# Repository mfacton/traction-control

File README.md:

# traction-control
Traction Control

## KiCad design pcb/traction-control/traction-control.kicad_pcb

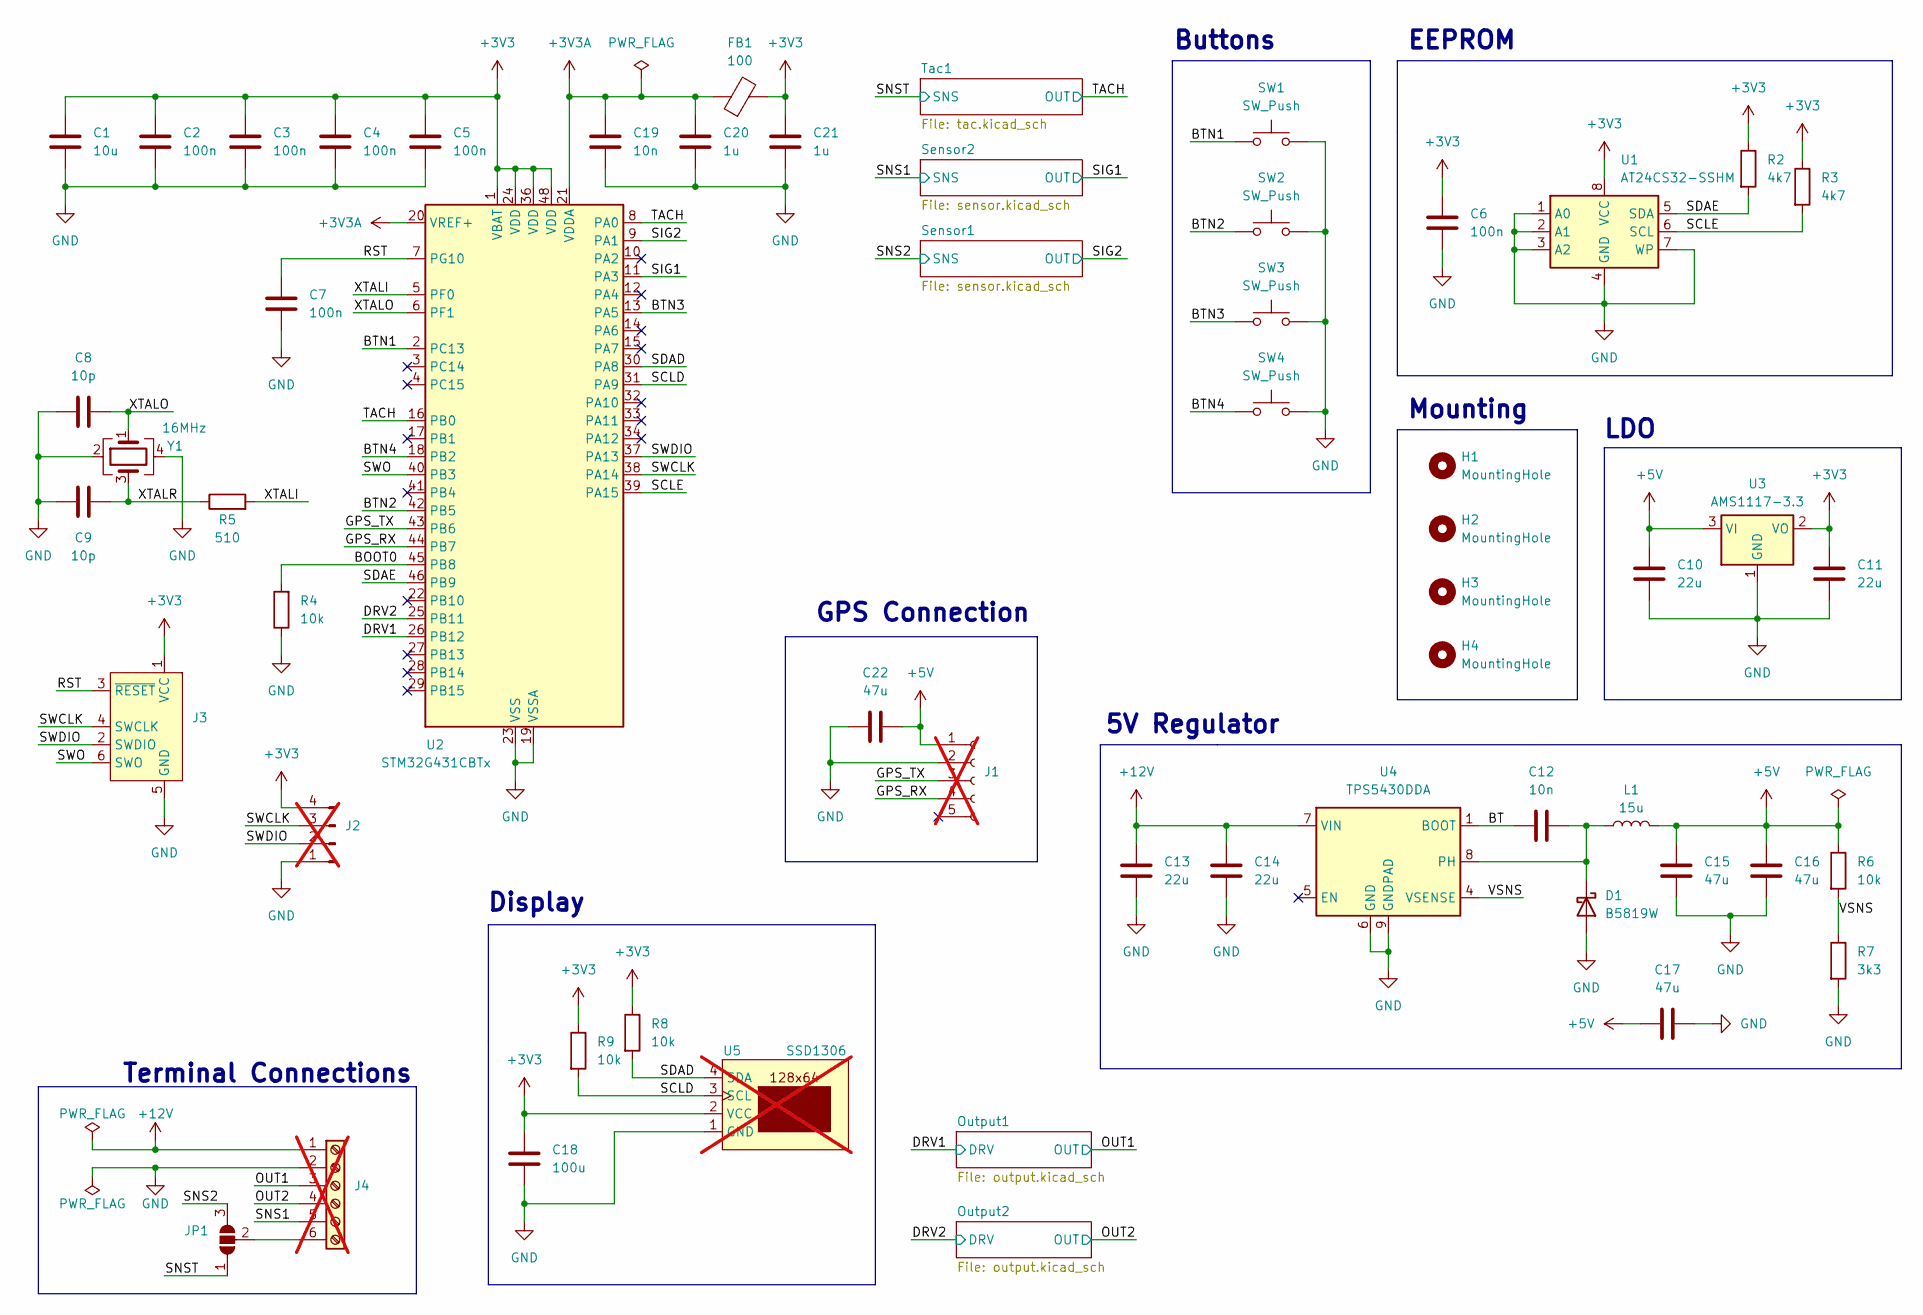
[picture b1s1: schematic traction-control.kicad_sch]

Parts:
C1: 10u; C_0402_1005Metric; LCSC C15525
C2, C3, C4, C5, C6, C7: 100n; C_0402_1005Metric; LCSC C1525
C8, C9: 10p; C_0402_1005Metric; LCSC C32949
C10: 22u; C_0805_2012Metric; LCSC C45783
C11: 22u; C_0603_1608Metric; LCSC C59461
C12, C19: 10n; C_0402_1005Metric; LCSC C15195
C13, C14: 22u; C_1206_3216Metric; LCSC C12891
C15, C16, C17, C22: 47u; C_1206_3216Metric; LCSC C96123
C18: 100u; C_1206_3216Metric; LCSC C15008
C20, C21: 1u; C_0402_1005Metric; LCSC C52923
D1: B5819W; D_SOD-123; LCSC C8598
FB1: 100; L_0805_2012Metric; LCSC C1015
H1, H2, H3, H4: MountingHole; MountingHole_3.2mm_M3
J1: Conn_01x05_Socket; PinHeader_1x05_P2.54mm_Vertical; not fitted
J2: Conn_01x04_Pin; PinHeader_1x04_P2.54mm_Vertical; not fitted
J3: Conn_ARM_SWD_TagConnect_TC2030-NL; Tag-Connect_TC2030-IDC-NL_2x03_P1.27mm_Vertical
J4: Screw_Terminal_01x06; ScrewTerminalPlug_6P_P5.08; not fitted
JP1: SolderJumper_3_Open; SolderJumper-3_P1.3mm_Open_RoundedPad1.0x1.5mm
L1: 15u; L_Changjiang_FNR6020S; LCSC C168015
R2, R3: 4k7; R_0402_1005Metric; LCSC C25900
R4, R6, R8, R9: 10k; R_0402_1005Metric; LCSC C25744
R5: 510; R_0402_1005Metric; LCSC C25123
R7: 3k3; R_0402_1005Metric; LCSC C25890
SW1, SW2, SW3, SW4: SW_Push; SW_Push_1P1T_NO_6x6mm_H9.5mm; LCSC C455119
U1: AT24CS32-SSHM; SOIC-8_3.9x4.9mm_P1.27mm; LCSC C6482
U2: STM32G431CBTx; LQFP-48_7x7mm_P0.5mm; LCSC C529355
U3: AMS1117-3.3; SOT-223-3_TabPin2; LCSC C6186
U4: TPS5430DDA; TI_SO-PowerPAD-8_ThermalVias; LCSC C9864
U5: SSD1306; SSD1309_1.3; not fitted
Y1: 16MHz; Crystal_SMD_3225-4Pin_3.2x2.5mm; LCSC C13738

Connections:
+3V3: C1.1, C2.1, C3.1, C4.1, C5.1, C6.1, C11.1, C18.1, C21.1, FB1.2, J2.4, J3.1 (VCC), R2.1, R3.1, R8.1, R9.1, U1.8 (VCC), U2.1 (VBAT), U2.24 (VDD), U2.36 (VDD), U2.48 (VDD), U3.2 (VO), U5.2 (VCC)
+3V3A: C19.1, C20.1, FB1.1, U2.20 (VREF+), U2.21 (VDDA)
+5V: C10.1, C15.1, C16.1, C17.1, C22.1, J1.1, L1.2, R6.1, U3.3 (VI)
+12V: C13.1, C14.1, J4.1, U4.7 (VIN); also elsewhere on the board
/BOOT0: R4.2, U2.45 (PB8)
/BT: C12.1, U4.1 (BOOT)
/BTN1: SW1.1, U2.2 (PC13)
/BTN2: SW2.1, U2.42 (PB5)
/BTN3: SW3.1, U2.13 (PA5)
/BTN4: SW4.1, U2.18 (PB2)
/DRV1: U2.26 (PB12); also elsewhere on the board
/DRV2: U2.25 (PB11); also elsewhere on the board
/GPS_RX: J1.4, U2.44 (PB7)
/GPS_TX: J1.3, U2.43 (PB6)
/OUT1: J4.3; also elsewhere on the board
/OUT2: J4.4; also elsewhere on the board
/RST: C7.1, J3.3 (~RESET), U2.7 (PG10)
/SCLD: R9.2, U2.31 (PA9), U5.3 (SCL)
/SCLE: R3.2, U1.6 (SCL), U2.39 (PA15)
/SDAD: R8.2, U2.30 (PA8), U5.4 (SDA)
/SDAE: R2.2, U1.5 (SDA), U2.46 (PB9)
/SIG1: U2.11 (PA3); also elsewhere on the board
/SIG2: U2.9 (PA1); also elsewhere on the board
/SNS1: J4.5; also elsewhere on the board
/SNS2: JP1.3 (B); also elsewhere on the board
/SNST: JP1.1 (A); also elsewhere on the board
/SWCLK: J2.3, J3.4 (SWCLK), U2.38 (PA14)
/SWDIO: J2.2, J3.2 (SWDIO), U2.37 (PA13)
/SWO: J3.6 (SWO), U2.40 (PB3)
/TACH: U2.8 (PA0), U2.16 (PB0); also elsewhere on the board
/VSNS: R6.2, R7.1, U4.4 (VSENSE)
/XTALI: R5.2, U2.5 (PF0)
/XTALO: C8.2, U2.6 (PF1), Y1.1
/XTALR: C9.2, R5.1, Y1.3
GND: C1.2, C2.2, C3.2, C4.2, C5.2, C6.2, C7.2, C8.1, C9.1, C10.2, C11.2, C13.2, C14.2, C15.2, C16.2, C17.2, C18.2, C19.2, C20.2, C21.2, C22.2, D1.2 (A), J1.2, J2.1, J3.5 (GND), J4.2, R4.1, R7.2, SW1.2, SW2.2, SW3.2, SW4.2, U1.1 (A0), U1.2 (A1), U1.3 (A2), U1.4 (GND), U1.7 (WP), U2.19 (VSSA), U2.23 (VSS), U2.35 (VSS), U2.47 (VSS), U3.1 (GND), U4.6 (GND), U4.9 (GNDPAD), U5.1 (GND), Y1.2, Y1.4; also elsewhere on the board
unnamed: C12.2, D1.1 (K), L1.1, U4.8 (PH)
unnamed: J4.6, JP1.2 (C)

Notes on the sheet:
GPS Connection
Mounting
EEPROM
LDO
Terminal Connections
5V Regulator
Display
Buttons

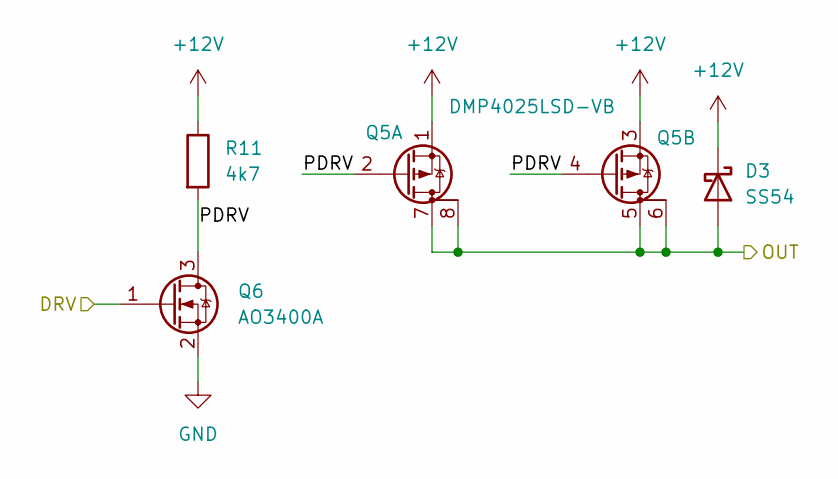
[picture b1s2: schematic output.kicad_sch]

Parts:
D3: SS54; D_SMA; LCSC C22452
Q5: DMP4025LSD-VB; SOP-8_3.9x4.9mm_P1.27mm; LCSC C725015
Q6: AO3400A; SOT-23; LCSC C20917
R11: 4k7; R_0402_1005Metric; LCSC C25900

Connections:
+12V: D3.1 (K), Q5.1 (S), Q5.3 (S), R11.1; also elsewhere on the board
/DRV2: Q6.1 (G); also elsewhere on the board
/OUT2: D3.2 (A), Q5.5 (D), Q5.6 (D), Q5.7 (D), Q5.8 (D); also elsewhere on the board
/Output2/PDRV: Q5.2 (G), Q5.4 (G), Q6.3 (D), R11.2
GND: Q6.2 (S); also elsewhere on the board

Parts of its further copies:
D2: SS54; D_SMA; LCSC C22452
Q3: DMP4025LSD-VB; SOP-8_3.9x4.9mm_P1.27mm; LCSC C725015
Q4: AO3400A; SOT-23; LCSC C20917
R10: 4k7; R_0402_1005Metric; LCSC C25900

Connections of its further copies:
+12V: D2.1 (K), Q3.1 (S), Q3.3 (S), R10.1; also elsewhere on the board
/DRV1: Q4.1 (G); also elsewhere on the board
/OUT1: D2.2 (A), Q3.5 (D), Q3.6 (D), Q3.7 (D), Q3.8 (D); also elsewhere on the board
/Output1/PDRV: Q3.2 (G), Q3.4 (G), Q4.3 (D), R10.2
GND: Q4.2 (S); also elsewhere on the board

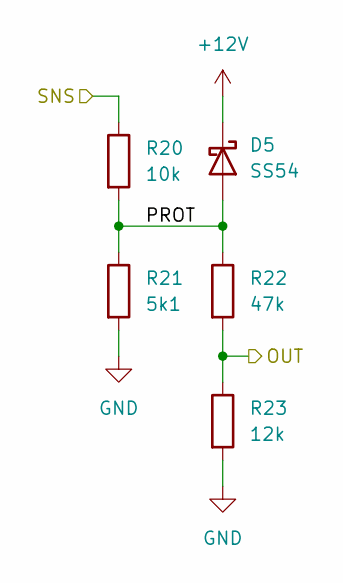
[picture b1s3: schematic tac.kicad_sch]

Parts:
D5: SS54; D_SMA; LCSC C22452
R20: 10k; R_0402_1005Metric; LCSC C25744
R21: 5k1; R_0402_1005Metric; LCSC C25905
R22: 47k; R_0402_1005Metric; LCSC C25792
R23: 12k; R_0402_1005Metric; LCSC C25752

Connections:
+12V: D5.1 (K); also elsewhere on the board
/SNST: R20.1; also elsewhere on the board
/TACH: R22.2, R23.1; also elsewhere on the board
/Tac1/PROT: D5.2 (A), R20.2, R21.1, R22.1
GND: R21.2, R23.2; also elsewhere on the board

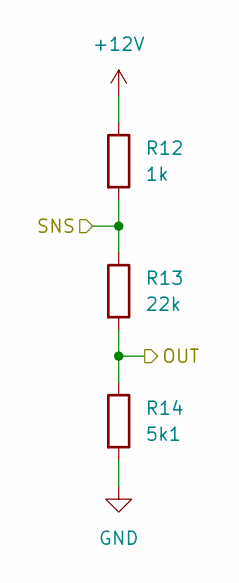
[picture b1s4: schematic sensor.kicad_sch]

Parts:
R12: 1k; R_1206_3216Metric; LCSC C4410
R13: 22k; R_0402_1005Metric; LCSC C25768
R14: 5k1; R_0402_1005Metric; LCSC C25905

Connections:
+12V: R12.1; also elsewhere on the board
/SIG1: R13.2, R14.1; also elsewhere on the board
/SNS1: R12.2, R13.1; also elsewhere on the board
GND: R14.2; also elsewhere on the board

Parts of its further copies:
R17: 1k; R_1206_3216Metric; LCSC C4410
R18: 22k; R_0402_1005Metric; LCSC C25768
R19: 5k1; R_0402_1005Metric; LCSC C25905

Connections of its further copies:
+12V: R17.1; also elsewhere on the board
/SIG2: R18.2, R19.1; also elsewhere on the board
/SNS2: R17.2, R18.1; also elsewhere on the board
GND: R19.2; also elsewhere on the board

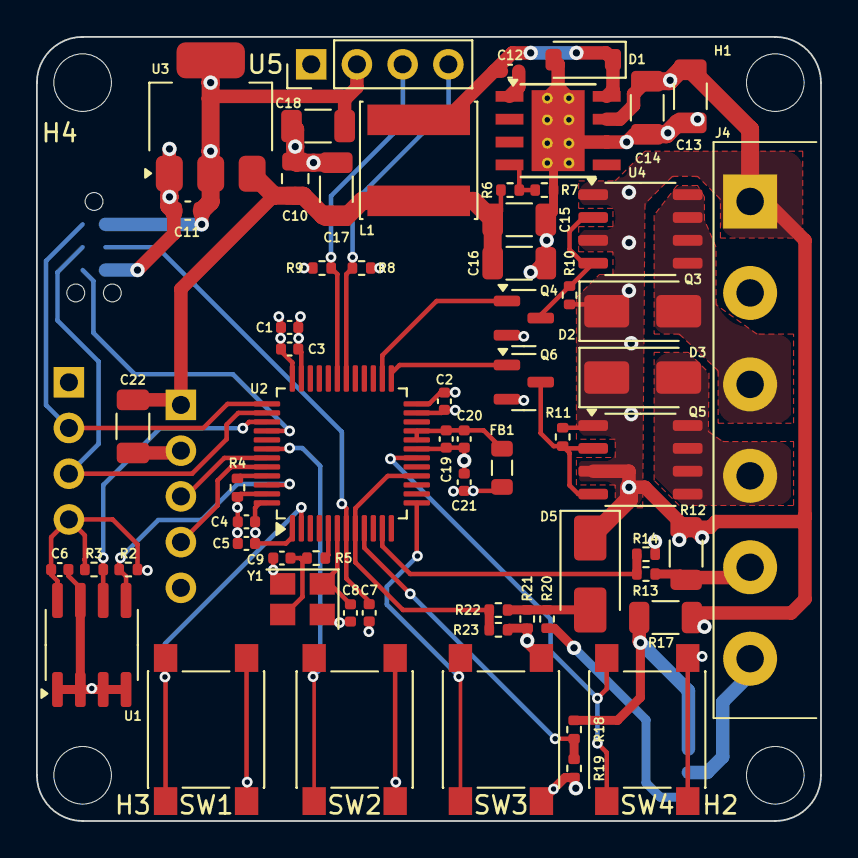
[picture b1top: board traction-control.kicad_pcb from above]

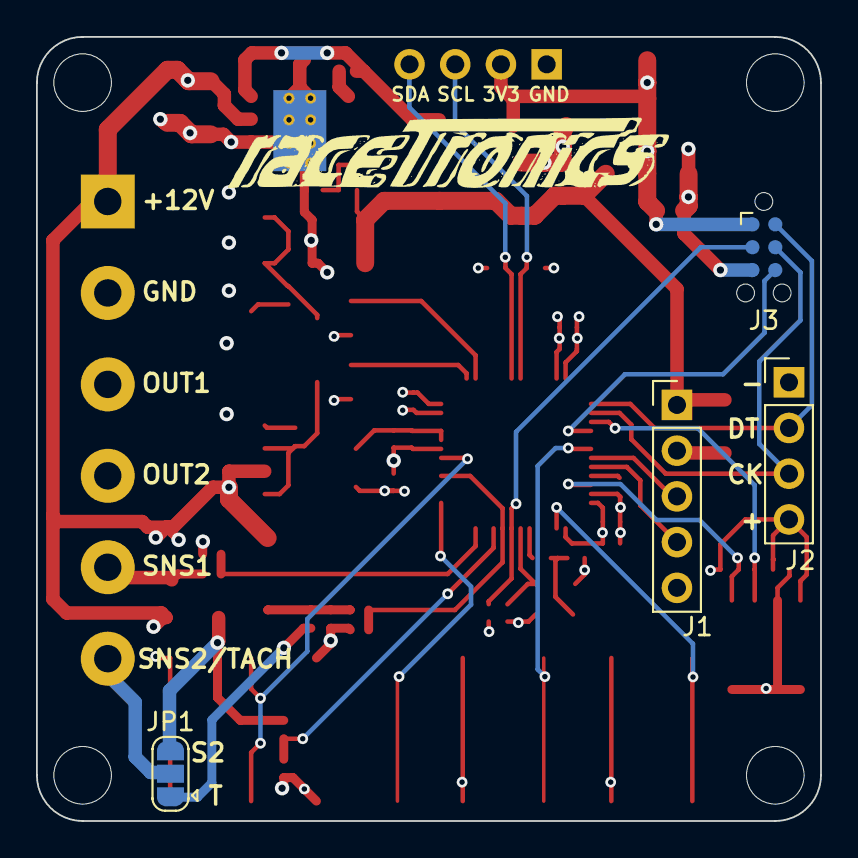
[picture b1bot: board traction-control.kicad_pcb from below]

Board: 4 copper layers, 43.6 x 43.6 mm, 72 parts (5 on the bottom side), 40 nets.

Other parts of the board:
G1: LOGO

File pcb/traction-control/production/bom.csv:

Designator,Footprint,Quantity,Value,LCSC Part #
C1,0402,1,10u,C15525
C10,0805,1,22u,C45783
C11,0603,1,22u,C59461
"C12, C19",0402,2,10n,C15195
"C13, C14",1206,2,22u,C12891
"C15, C16, C17, C22",1206,4,47u,C96123
C18,1206,1,100u,C15008
"C2, C3, C4, C5, C6, C7",0402,6,100n,C1525
"C20, C21",0402,2,1u,C52923
"C8, C9",0402,2,10p,C32949
D1,D_SOD-123,1,B5819W,C8598
"D2, D3, D5",D_SMA,3,SS54,C22452
FB1,0805,1,100,C1015
L1,L_Changjiang_FNR6020S,1,15u,C168015
"Q3, Q5",SOP-8_3.9x4.9mm_P1.27mm,2,DMP4025LSD-VB,C725015
"Q4, Q6",SOT-23,2,AO3400A,C20917
"R10, R11, R2, R3",0402,4,4k7,C25900
"R12, R17",1206,2,1k,C4410
"R13, R18",0402,2,22k,C25768
"R14, R19, R21",0402,3,5k1,C25905
"R20, R6, R8, R9",0402,4,10k,C25744
R22,0402,1,47k,C25792
R23,0402,1,12k,C25752
R4,0402,1,10k, C25744
R5,0402,1,510,C25123
R7,0402,1,3k3,C25890
"SW1, SW2, SW3, SW4",SW_Push_1P1T_NO_6x6mm_H9.5mm,4,SW_Push,C455119
U1,SOIC-8_3.9x4.9mm_P1.27mm,1,AT24CS32-SSHM,C6482
U2,LQFP-48_7x7mm_P0.5mm,1,STM32G431CBTx,C529355
U3,SOT-223-3_TabPin2,1,AMS1117-3.3,C6186
U4,TI_SO-PowerPAD-8_ThermalVias,1,TPS5430DDA,C9864
Y1,Crystal_SMD_3225-4Pin_3.2x2.5mm,1,16MHz,C13738

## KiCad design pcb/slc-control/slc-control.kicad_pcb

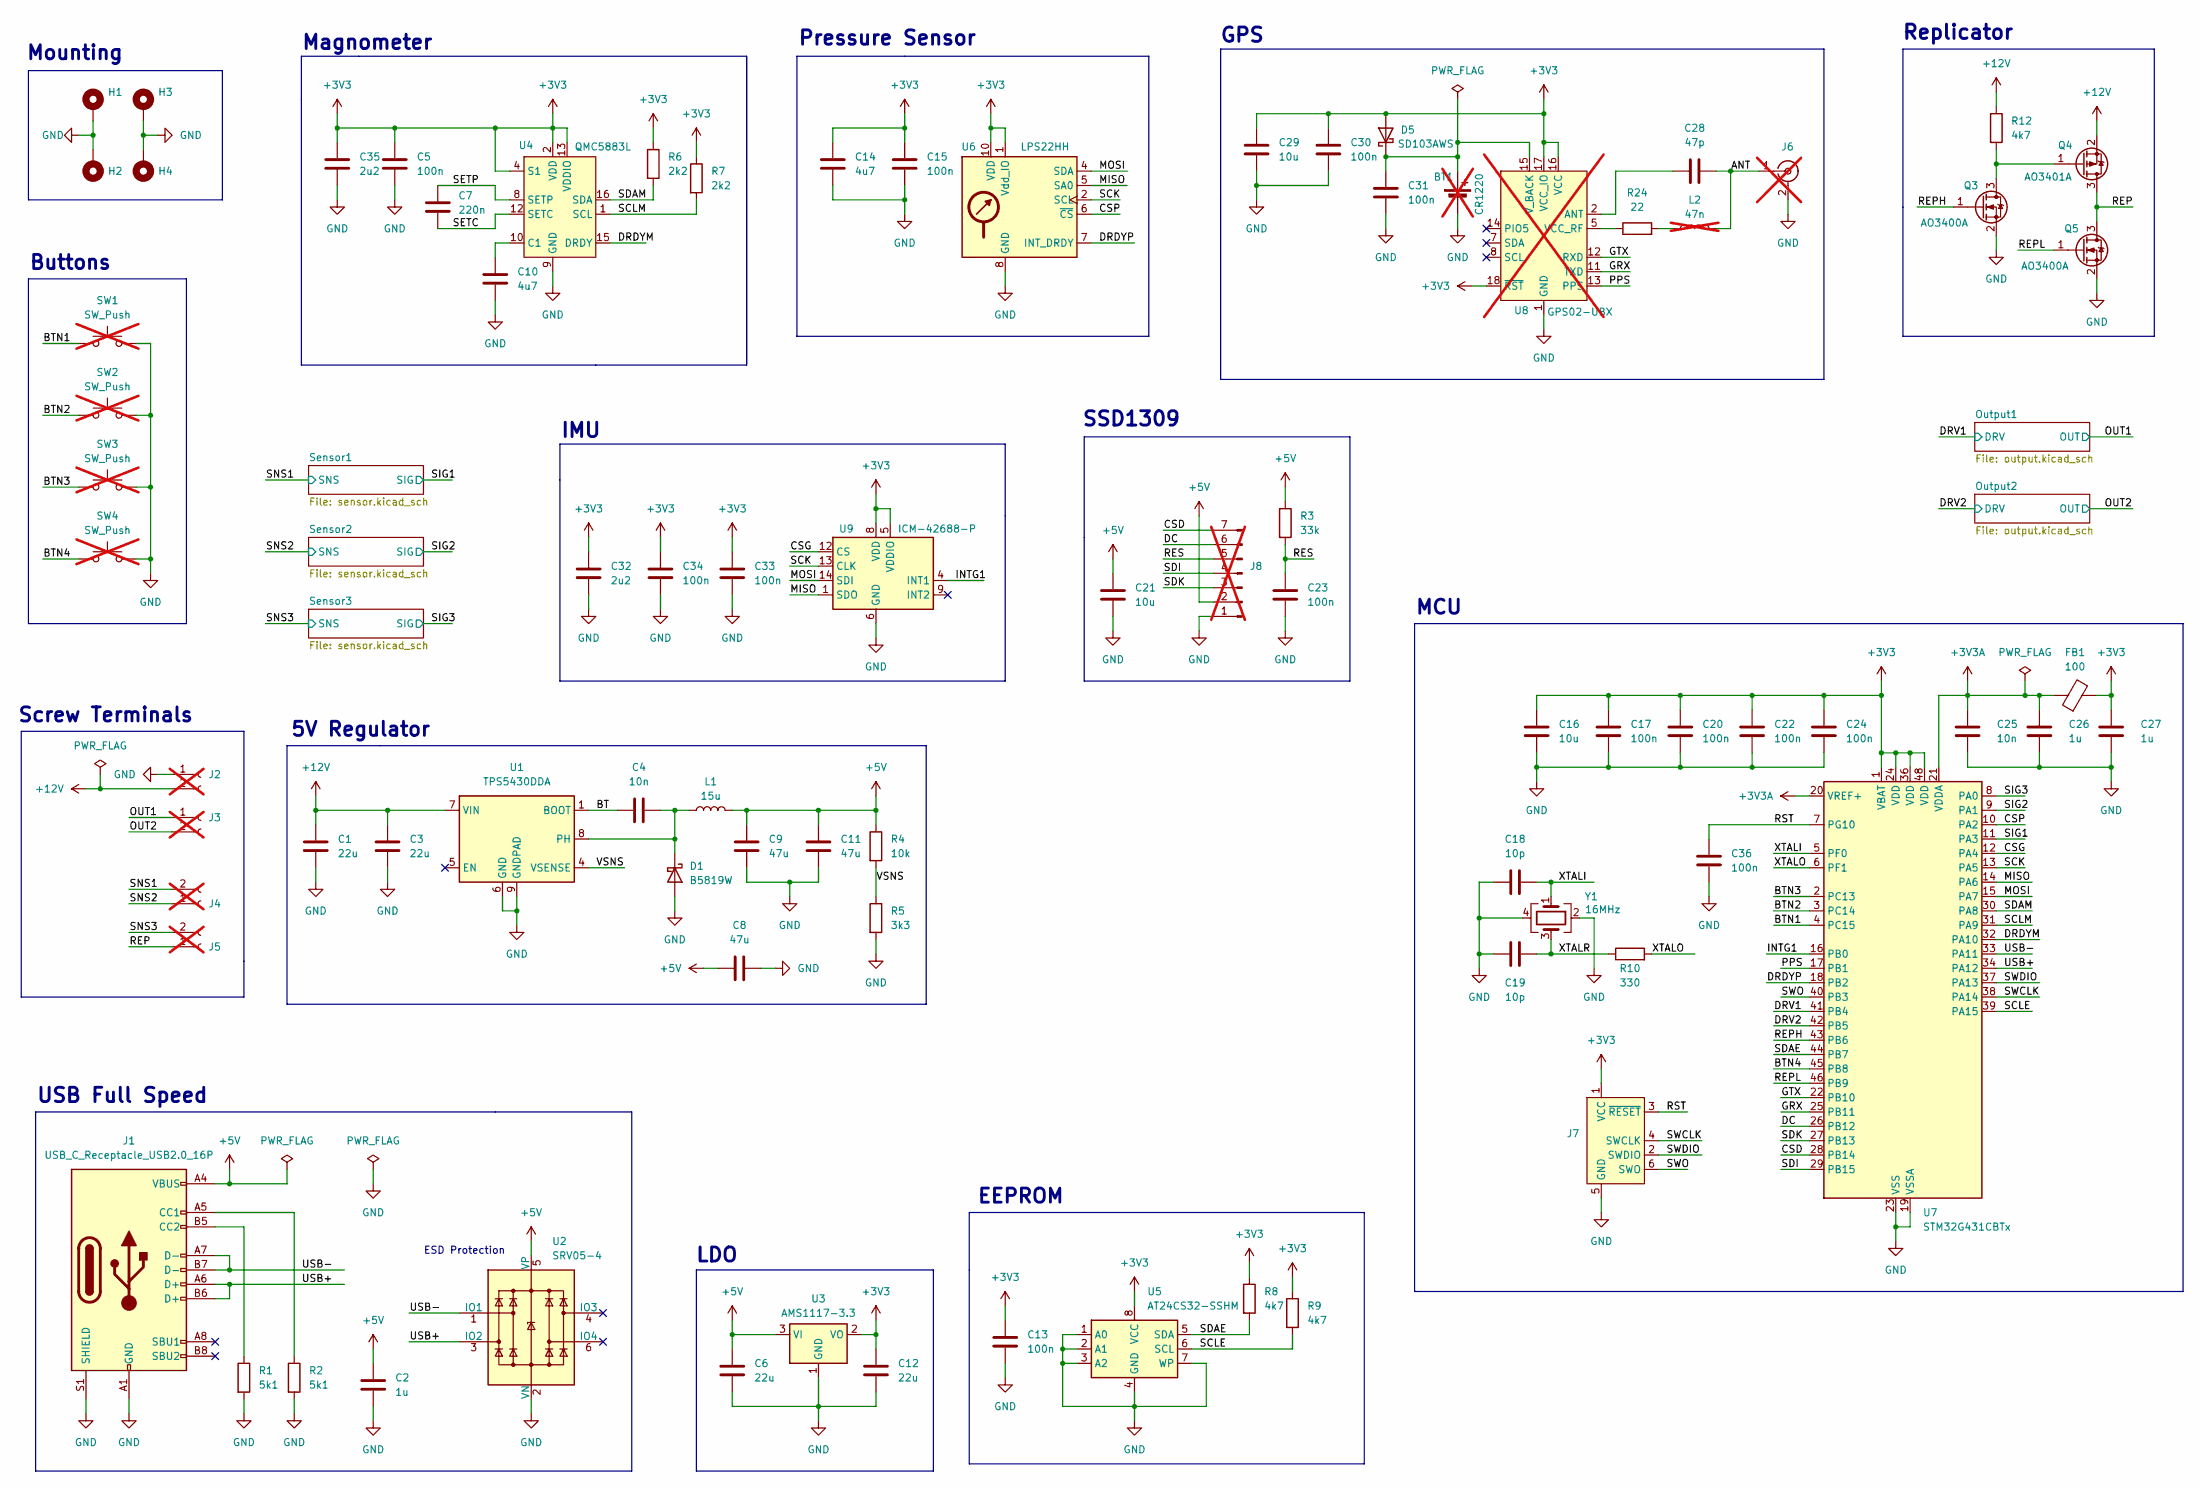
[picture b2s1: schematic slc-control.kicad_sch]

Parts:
BT1: CR1220; LCSC C70381; not fitted
C1, C3: 22u; C_1206_3216Metric; LCSC C12891
C2, C26, C27: 1u; C_0402_1005Metric; LCSC C52923
C4, C25: 10n; C_0402_1005Metric; LCSC C15195
C5, C13, C15, C17, C20, C22, C23, C24, C30, C31, C33, C34, C36: 100n; C_0402_1005Metric; LCSC C1525
C6: 22u; C_0805_2012Metric; LCSC C45783
C7: 220n; C_0402_1005Metric; LCSC C16772
C8, C9, C11: 47u; C_1206_3216Metric; LCSC C96123
C10: 4u7; C_0603_1608Metric; LCSC C19666
C12: 22u; C_0603_1608Metric; LCSC C59461
C14: 4u7; C_0402_1005Metric; LCSC C23733
C16, C21, C29: 10u; C_0603_1608Metric; LCSC C19702
C18, C19: 10p; C_0402_1005Metric; LCSC C32949
C28: 47p; C_0402_1005Metric; LCSC C1567
C32, C35: 2u2; C_0402_1005Metric; LCSC C12530
D1: B5819W; D_SOD-123; LCSC C8598
D5: SD103AWS; D_SOD-323; LCSC C7420360
FB1: 100; L_0805_2012Metric; LCSC C1015
H1, H2, H3, H4: MountingHole_Pad; MountingHole_5.3mm_M5_ISO7380_Pad
J1: USB_C_Receptacle_USB2.0_16P; USB_C_Receptacle_GCT_USB4105-xx-A_16P_TopMnt_Horizontal; LCSC C2765186
J2, J3, J4, J5: Conn_01x02_Socket; WJ126V-5.0-2P; LCSC C8404; not fitted
J6: Conn_Coaxial; BWSMA-KWE-Z001; LCSC C496551; not fitted
J7: Conn_ARM_SWD_TagConnect_TC2030-NL; Tag-Connect_TC2030-IDC-NL_2x03_P1.27mm_Vertical
J8: Conn_01x07_Pin; PinHeader_1x07_P2.54mm_Vertical; not fitted
L1: 15u; L_Changjiang_FNR6020S; LCSC C168015
L2: 47n; L_0603_1608Metric; LCSC C98076; not fitted
Q3, Q5: AO3400A; SOT-23; LCSC C20917
Q4: AO3401A; SOT-23; LCSC C15127
R1, R2: 5k1; R_0402_1005Metric; LCSC C25905
R3: 33k; R_0402_1005Metric; LCSC C25779
R4: 10k; R_0402_1005Metric; LCSC C25744
R5: 3k3; R_0402_1005Metric; LCSC C25890
R6, R7: 2k2; R_0402_1005Metric; LCSC C25879
R8, R9, R12: 4k7; R_0402_1005Metric; LCSC C25900
R10: 330; R_0402_1005Metric; LCSC C25104
R24: 22; R_0402_1005Metric; LCSC C25092
SW1, SW2, SW3, SW4: SW_Push; SW_PUSH_6mm_H9.5mm; LCSC C455119; not fitted
U1: TPS5430DDA; TI_SO-PowerPAD-8_ThermalVias; LCSC C9864
U2: SRV05-4; SOT-23-6; LCSC C7420376
U3: AMS1117-3.3; SOT-223-3_TabPin2; LCSC C6186
U4: QMC5883L; LGA-16_3x3mm_P0.5mm
U5: AT24CS32-SSHM; SOIC-8_3.9x4.9mm_P1.27mm; LCSC C6482
U6: LPS22HH; ST_HLGA-10_2x2mm_P0.5mm_LayoutBorder3x2y; LCSC C2827824
U7: STM32G431CBTx; LQFP-48_7x7mm_P0.5mm; LCSC C529355
U8: GPS02-UBX; LCSC C5356636; not fitted
U9: ICM-42688-P; LGA-14_3x2.5mm_P0.5mm_LayoutBorder3x4y; LCSC C1850418
Y1: 16MHz; Crystal_SMD_3225-4Pin_3.2x2.5mm; LCSC C13738

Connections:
+3V3: C5.1, C12.1, C13.1, C14.1, C15.1, C16.1, C17.1, C20.1, C22.1, C24.1, C27.1, C29.1, C30.1, C32.1, C33.1, C34.1, C35.1, D5.2 (A), FB1.2, J7.1 (VCC), R6.1, R7.1, R8.1, R9.1, U3.2 (VO), U4.2 (VDD), U4.4 (S1), U4.13 (VDDIO), U5.8 (VCC), U6.1 (Vdd_IO), U6.10 (VDD), U7.1 (VBAT), U7.24 (VDD), U7.36 (VDD), U7.48 (VDD), U8.16 (VCC), U8.17 (VCC_IO), U8.18 (~RST), U9.5 (VDDIO), U9.8 (VDD)
+3V3A: C25.1, C26.1, FB1.1, U7.20 (VREF+), U7.21 (VDDA)
+5V: C2.1, C6.1, C8.1, C9.1, C11.1, C21.1, J1.A4 (VBUS), J1.A9 (VBUS), J1.B4 (VBUS), J1.B9 (VBUS), J8.2, L1.2, R3.1, R4.1, U2.5 (VP), U3.3 (VI)
+12V: C1.1, C3.1, J2.2, Q4.2 (S), R12.1, U1.7 (VIN); also elsewhere on the board
/ANT: C28.2, J6.1 (In), L2.2
/BT: C4.1, U1.1 (BOOT)
/BTN1: SW1.1, U7.4 (PC15)
/BTN2: SW2.1, U7.3 (PC14)
/BTN3: SW3.1, U7.2 (PC13)
/BTN4: SW4.1, U7.45 (PB8)
/CSD: J8.7, U7.28 (PB14)
/CSG: U7.12 (PA4), U9.12 (CS)
/CSP: U6.6 (~CS), U7.10 (PA2)
/DC: J8.6, U7.26 (PB12)
/DRDYM: U4.15 (DRDY), U7.32 (PA10)
/DRDYP: U6.7 (INT_DRDY), U7.18 (PB2)
/DRV1: U7.41 (PB4); also elsewhere on the board
/DRV2: U7.42 (PB5); also elsewhere on the board
/GRX: U7.25 (PB11), U8.11 (TXD)
/GTX: U7.22 (PB10), U8.12 (RXD)
/INTG1: U7.16 (PB0), U9.4 (INT1)
/MISO: U6.5 (SA0), U7.14 (PA6), U9.1 (SDO)
/MOSI: U6.4 (SDA), U7.15 (PA7), U9.14 (SDI)
/OUT1: J3.1; also elsewhere on the board
/OUT2: J3.2; also elsewhere on the board
/PPS: U7.17 (PB1), U8.13 (PPS)
/REP: J5.1, Q4.3 (D), Q5.3 (D)
/REPH: Q3.1 (G), U7.43 (PB6)
/REPL: Q5.1 (G), U7.46 (PB9)
/RES: C23.1, J8.5, R3.2
/RST: C36.1, J7.3 (~RESET), U7.7 (PG10)
/SCK: U6.2 (SCL), U7.13 (PA5), U9.13 (CLK)
/SCLE: R9.2, U5.6 (SCL), U7.39 (PA15)
/SCLM: R7.2, U4.1 (SCL), U7.31 (PA9)
/SDAE: R8.2, U5.5 (SDA), U7.44 (PB7)
/SDAM: R6.2, U4.16 (SDA), U7.30 (PA8)
/SDI: J8.4, U7.29 (PB15)
/SDK: J8.3, U7.27 (PB13)
/SETC: C7.2, U4.12 (SETC)
/SETP: C7.1, U4.8 (SETP)
/SIG1: U7.11 (PA3); also elsewhere on the board
/SIG2: U7.9 (PA1); also elsewhere on the board
/SIG3: U7.8 (PA0); also elsewhere on the board
/SNS1: J4.2; also elsewhere on the board
/SNS2: J4.1; also elsewhere on the board
/SNS3: J5.2; also elsewhere on the board
/SWCLK: J7.4 (SWCLK), U7.38 (PA14)
/SWDIO: J7.2 (SWDIO), U7.37 (PA13)
/SWO: J7.6 (SWO), U7.40 (PB3)
/USB+: J1.A6 (D+), J1.B6 (D+), U2.3 (IO2), U7.34 (PA12)
/USB-: J1.A7 (D-), J1.B7 (D-), U2.1 (IO1), U7.33 (PA11)
/VSNS: R4.2, R5.1, U1.4 (VSENSE)
/XTALI: C18.2, U7.5 (PF0), Y1.1
/XTALO: R10.2, U7.6 (PF1)
/XTALR: C19.2, R10.1, Y1.3
GND: BT1.2 (-), C1.2, C2.2, C3.2, C5.2, C6.2, C8.2, C9.2, C10.2, C11.2, C12.2, C13.2, C14.2, C15.2, C16.2, C17.2, C18.1, C19.1, C20.2, C21.2, C22.2, C23.2, C24.2, C25.2, C26.2, C27.2, C29.2, C30.2, C31.2, C32.2, C33.2, C34.2, C35.2, C36.2, D1.2 (A), H1.1, H2.1, H3.1, H4.1, J1.A1 (GND), J1.A12 (GND), J1.B1 (GND), J1.B12 (GND), J1.S1 (SHIELD), J2.1, J6.2 (Ext), J7.5 (GND), J8.1, Q3.2 (S), Q5.2 (S), R1.2, R2.2, R5.2, SW1.2, SW2.2, SW3.2, SW4.2, U1.6 (GND), U1.9 (GNDPAD), U2.2 (VN), U3.1 (GND), U4.9 (GND), U4.11 (GND), U5.1 (A0), U5.2 (A1), U5.3 (A2), U5.4 (GND), U5.7 (WP), U6.3 (GND), U6.8 (GND), U6.9 (GND), U7.19 (VSSA), U7.23 (VSS), U7.35 (VSS), U7.47 (VSS), U8.1 (GND), U8.3 (GND), U8.10 (GND), U9.6 (GND), U9.7 (RESV), U9.11 (RESV), Y1.2, Y1.4; also elsewhere on the board
unnamed: BT1.1 (+), C31.1, D5.1 (K), U8.15 (V_BACK)
unnamed: C4.2, D1.1 (K), L1.1, U1.8 (PH)
unnamed: J1.A5 (CC1), R2.1
unnamed: J1.B5 (CC2), R1.1
unnamed: L2.1, R24.2
unnamed: Q3.3 (D), Q4.1 (G), R12.2
unnamed: C10.1, U4.10 (C1)
unnamed: C28.1, U8.2 (ANT)
unnamed: R24.1, U8.5 (VCC_RF)

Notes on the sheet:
5V Regulator
Mounting
USB Full Speed
Buttons
Magnometer
Screw Terminals
ESD Protection
GPS
SSD1309
Pressure Sensor
IMU
Replicator
LDO
MCU
EEPROM

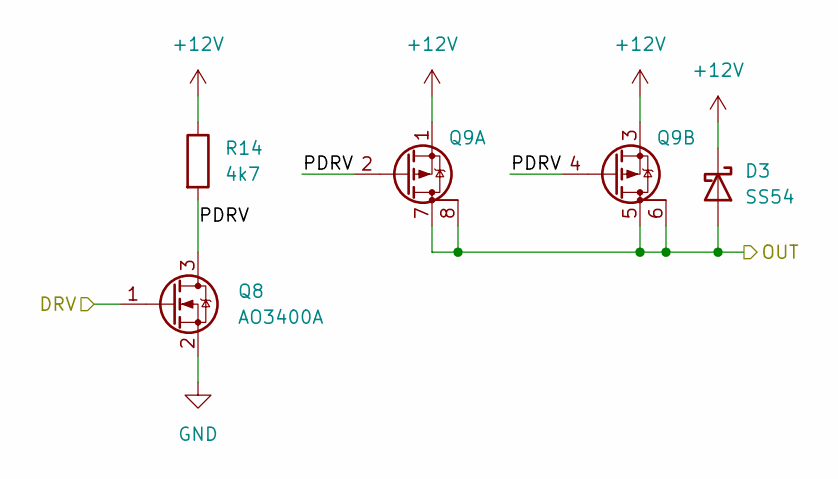
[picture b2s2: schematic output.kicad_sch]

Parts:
D3: SS54; D_SMA; LCSC C22452
Q8: AO3400A; SOT-23; LCSC C20917
Q9: Q_Dual_PMOS_S1G1S2G2D2D2D1D1; SO-8_3.9x4.9mm_P1.27mm; LCSC C725015
R14: 4k7; R_0402_1005Metric; LCSC C25900

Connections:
+12V: D3.1 (K), Q9.1 (S), Q9.3 (S), R14.1; also elsewhere on the board
/DRV2: Q8.1 (G); also elsewhere on the board
/OUT2: D3.2 (A), Q9.5 (D), Q9.6 (D), Q9.7 (D), Q9.8 (D); also elsewhere on the board
/Output2/PDRV: Q8.3 (D), Q9.2 (G), Q9.4 (G), R14.2
GND: Q8.2 (S); also elsewhere on the board

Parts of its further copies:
D2: SS54; D_SMA; LCSC C22452
Q6: AO3400A; SOT-23; LCSC C20917
Q7: Q_Dual_PMOS_S1G1S2G2D2D2D1D1; SO-8_3.9x4.9mm_P1.27mm; LCSC C725015
R13: 4k7; R_0402_1005Metric; LCSC C25900

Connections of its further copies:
+12V: D2.1 (K), Q7.1 (S), Q7.3 (S), R13.1; also elsewhere on the board
/DRV1: Q6.1 (G); also elsewhere on the board
/OUT1: D2.2 (A), Q7.5 (D), Q7.6 (D), Q7.7 (D), Q7.8 (D); also elsewhere on the board
/Output1/PDRV: Q6.3 (D), Q7.2 (G), Q7.4 (G), R13.2
GND: Q6.2 (S); also elsewhere on the board

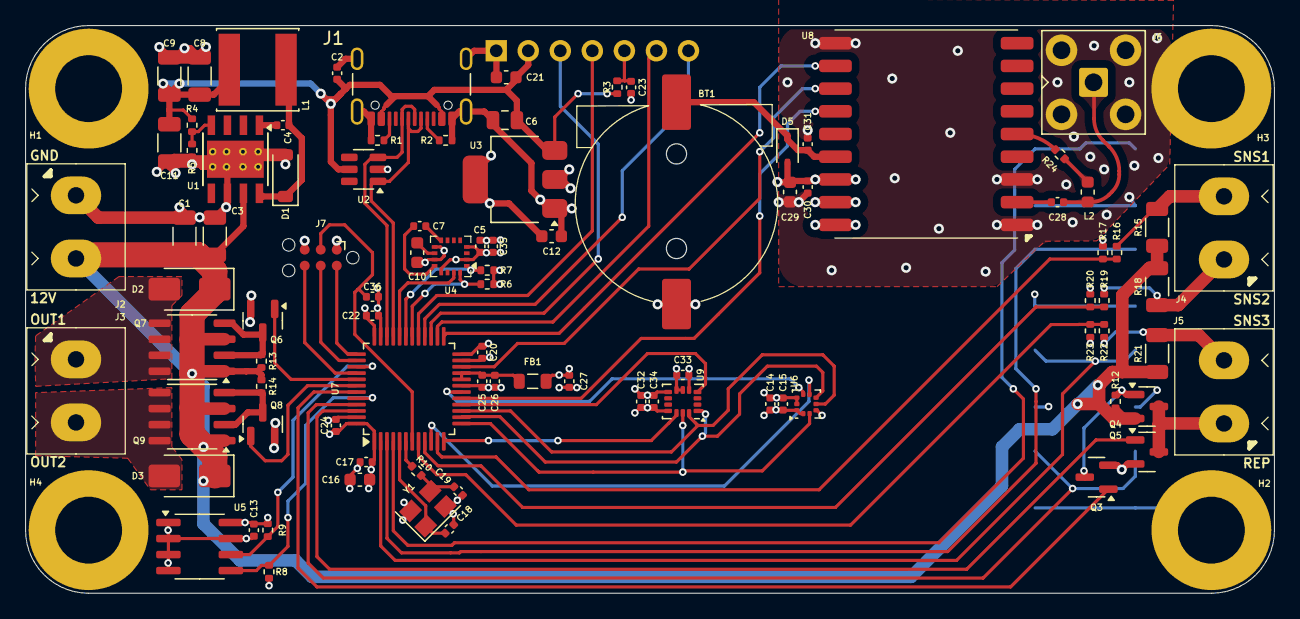
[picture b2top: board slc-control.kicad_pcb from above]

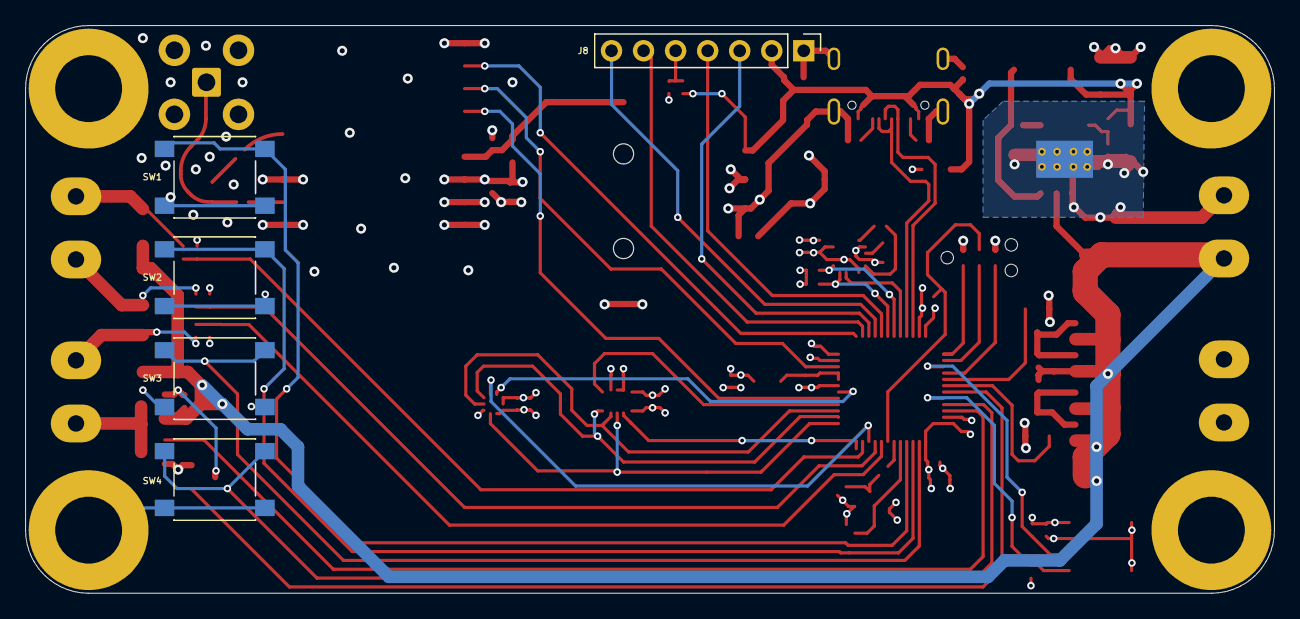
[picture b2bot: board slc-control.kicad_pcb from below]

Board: 4 copper layers, 99.0 x 45.0 mm, 100 parts (5 on the bottom side), 67 nets.

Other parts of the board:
R15, R18, R21: 1k; R_1206_3216Metric
R16, R19, R22: 33k; R_0402_1005Metric
R17, R20, R23: 10k; R_0402_1005Metric

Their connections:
+12V: R15.1, R18.1, R21.1; also elsewhere on the board
/SIG1: R16.2, R17.1; also elsewhere on the board
/SIG2: R19.2, R20.1; also elsewhere on the board
/SIG3: R22.2, R23.1; also elsewhere on the board
/SNS1: R15.2, R16.1; also elsewhere on the board
/SNS2: R18.2, R19.1; also elsewhere on the board
/SNS3: R21.2, R22.1; also elsewhere on the board
GND: R17.2, R20.2, R23.2; also elsewhere on the board

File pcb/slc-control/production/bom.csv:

Designator,Footprint,Quantity,Value,LCSC Part #
BT1,CR1220,1,CR1220,C70381
"C1, C3",1206,2,22u,C12891
C10,0603,1,4u7,C19666
"C11, C8, C9",1206,3,47u,C96123
C12,0603,1,22u,C59461
"C13, C15, C17, C20, C22, C23, C24, C30, C31, C33, C34, C36, C5",0402,13,100n,C1525
C14,0402,1,4u7,C23733
"C16, C21, C29",0603,3,10u,C19702
"C18, C19",0402,2,10p,C32949
"C2, C26, C27",0402,3,1u,C52923
"C25, C4",0402,2,10n,C15195
C28,0402,1,47p,C1567
"C32, C35",0402,2,2u2,C12530
C6,0805,1,22u,C45783
C7,0402,1,220n,C16772
D1,D_SOD-123,1,B5819W,C8598
"D2, D3",D_SMA,2,SS54,C22452
D5,D_SOD-323,1,SD103AWS,C7420360
FB1,0805,1,100,C1015
J1,USB_C_Receptacle_GCT_USB4105-xx-A_16P_TopMnt_Horizontal,1,USB_C_Receptacle_USB2.0_16P,C2765186
"J2, J3, J4, J5",WJ126V-5.0-2P,4,Conn_01x02_Socket,C8404
J6,BWSMA-KWE-Z001,1,Conn_Coaxial,C496551
L1,L_Changjiang_FNR6020S,1,15u,C168015
L2,0603,1,47n,C98076
"Q3, Q5, Q6, Q8",SOT-23,4,AO3400A,C20917
Q4,SOT-23,1,AO3401A,C15127
"Q7, Q9",SO-8_3.9x4.9mm_P1.27mm,2,Q_Dual_PMOS_S1G1S2G2D2D2D1D1,C725015
"R1, R2",0402,2,5k1,C25905
R10,0402,1,330,C25104
"R12, R13, R14, R8",0402,4,4k7,C25900
"R15, R18, R21",1206,3,1k,C4410
"R16, R19, R22, R3",0402,4,33k,C25779
"R17, R20, R23, R4",0402,4,10k,C25744
R24,0402,1,22,C25092
R5,0402,1,3k3,C25890
"R6, R7",0402,2,2k2,C25879
R9,0402,1,4k7,
"SW1, SW2, SW3, SW4",SW_PUSH_6mm_H9.5mm,4,SW_Push,C455119
U1,TI_SO-PowerPAD-8_ThermalVias,1,TPS5430DDA,C9864
U2,SOT-23-6,1,SRV05-4,C7420376
U3,SOT-223-3_TabPin2,1,AMS1117-3.3,C6186
U4,LGA-16_3x3mm_P0.5mm,1,QMC5883L,
U5,SOIC-8_3.9x4.9mm_P1.27mm,1,AT24CS32-SSHM,C6482
U6,ST_HLGA-10_2x2mm_P0.5mm_LayoutBorder3x2y,1,LPS22HH,C2827824
U7,LQFP-48_7x7mm_P0.5mm,1,STM32G431CBTx,C529355
U8,GPS02-UBX,1,GPS02-UBX,C5356636
U9,LGA-14_3x2.5mm_P0.5mm_LayoutBorder3x4y,1,ICM-42688-P,C1850418
Y1,Crystal_SMD_3225-4Pin_3.2x2.5mm,1,16MHz,C13738
